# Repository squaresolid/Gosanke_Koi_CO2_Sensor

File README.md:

# UROS-CO2_brkout
## UROŠ - Breakout board for the Sensirion SCD41 CO2 sensor

**UROŠ - Ubiquitous Rural Open Science Hardware**, is a collaborative, regional and globally connected research project bringing together people from the Hackteria network, the global GOSH and preparing regional activities in Maribor, Slovenia. It is supported through the kons-platform.

More info on UROŠ on the hackteria wiki: https://www.hackteria.org/wiki/UROS

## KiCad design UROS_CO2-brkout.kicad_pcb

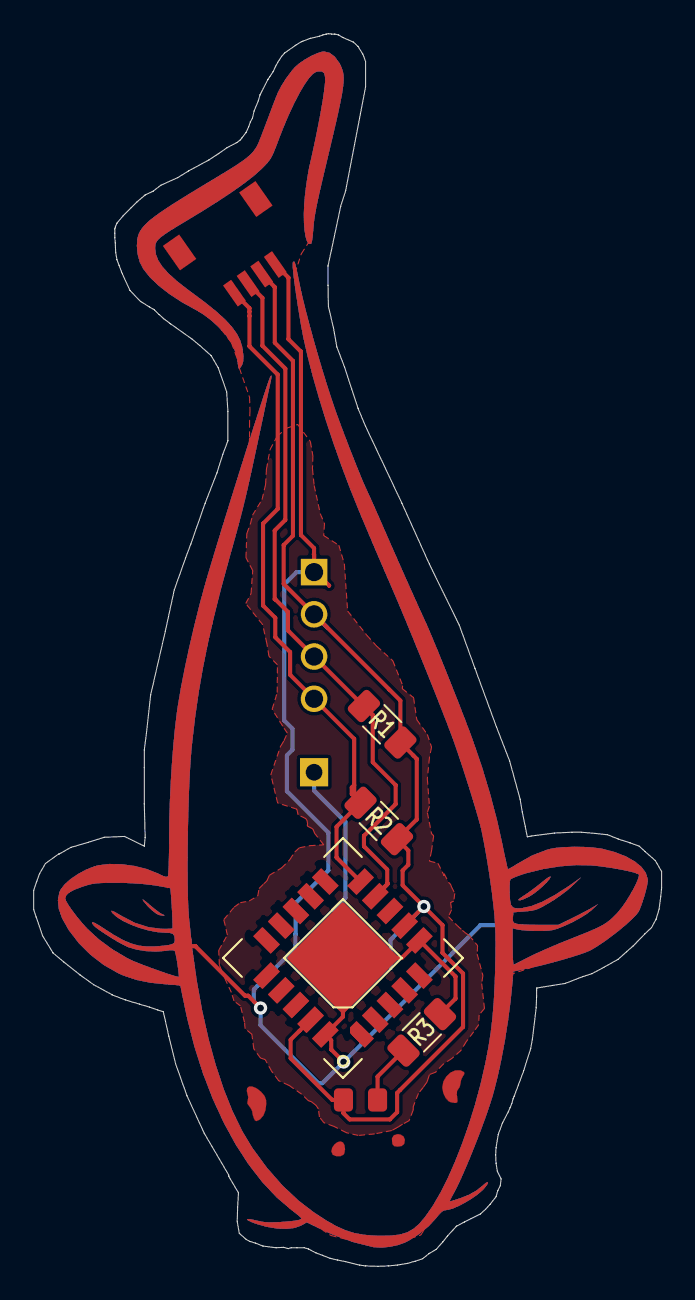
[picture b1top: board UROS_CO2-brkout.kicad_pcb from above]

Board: 2 copper layers, 37.8 x 74.1 mm, 10 parts (1 on the bottom side), 6 nets.

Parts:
CONN1: Adafruit_SCD-41-eagle-import_STEMMA_I2C_QT; JST_SH4_3D_connector
D1: LED; LED_0805_HandSolder
D2: WS2812B; NEO-Pixel_WS2812B
J2: Conn_01x04; HEADER-4P_new
J3: Conn_01x01; PinHeader_1x01
J4: CONN_02; tancho_out
R1, R2, R3: 10k; R_1206_HandSolder
U1: SCD41; SCD41_3D

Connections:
GND: CONN1.1, D2.3, J2.1, J4.1, J4.2, R3.2, U1.6, U1.20, U1.21
NEO_IN: D2.4, J3.1
unnamed: D1.1, R3.1
SCL: CONN1.3, J2.3, R1.1, U1.9
SDA: CONN1.4, J2.4, R2.1, U1.10
VCC: CONN1.2, D1.2, D2.1, J2.2, R1.2, R2.2, U1.7, U1.19

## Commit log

2022-10-07 Add files via upload
    Add Gerber
2022-10-07 Add files via upload
    Koi design
